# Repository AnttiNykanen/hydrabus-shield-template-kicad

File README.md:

# HydraBus shield template for KiCad

By Antti Nykänen <aon@umetronics.com>

This is a template project for making a [HydraBus](http://hydrabus.com/) shield with [KiCad](http://kicad-pcb.org/). It is based on the [Eagle template](https://github.com/bvernoux/hydrabus/tree/master/hardware/HydraBus_1_0_Shield_Template_Rev0) by Benjamin Vernoux. 

This work is licensed under a [Creative Commons Attribution-ShareAlike 4.0 International License](http://creativecommons.org/licenses/by-sa/4.0/)

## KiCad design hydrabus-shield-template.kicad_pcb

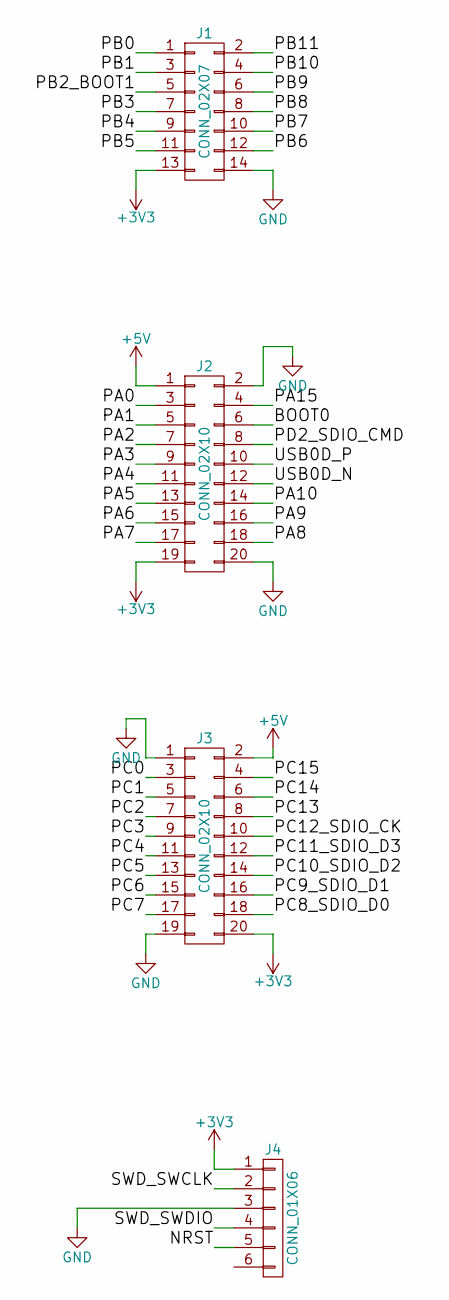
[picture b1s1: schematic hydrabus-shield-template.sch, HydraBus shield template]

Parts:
J1: CONN_02X07; Pin_Header_Straight_2x07
J2, J3: CONN_02X10; Pin_Header_Straight_2x10
J4: CONN_01X06; Pin_Header_Straight_1x06

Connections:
+3V3: J1.13, J2.19, J3.20, J4.1
+5V: J2.1, J3.2
/BOOT0: J2.6
/NRST: J4.5
/PA0: J2.3
/PA1: J2.5
/PA2: J2.7
/PA3: J2.9
/PA4: J2.11
/PA5: J2.13
/PA6: J2.15
/PA7: J2.17
/PA8: J2.18
/PA9: J2.16
/PA10: J2.14
/PA15: J2.4
/PB0: J1.1
/PB1: J1.3
/PB2_BOOT1: J1.5
/PB3: J1.7
/PB4: J1.9
/PB5: J1.11
/PB6: J1.12
/PB7: J1.10
/PB8: J1.8
/PB9: J1.6
/PB10: J1.4
/PB11: J1.2
/PC0: J3.3
/PC1: J3.5
/PC2: J3.7
/PC3: J3.9
/PC4: J3.11
/PC5: J3.13
/PC6: J3.15
/PC7: J3.17
/PC8_SDIO_D0: J3.18
/PC9_SDIO_D1: J3.16
/PC10_SDIO_D2: J3.14
/PC11_SDIO_D3: J3.12
/PC12_SDIO_CK: J3.10
/PC13: J3.8
/PC14: J3.6
/PC15: J3.4
/PD2_SDIO_CMD: J2.8
/SWD_SWCLK: J4.2
/SWD_SWDIO: J4.4
/USB0D_N: J2.12
/USB0D_P: J2.10
GND: J1.14, J2.2, J2.20, J3.1, J3.19, J4.3

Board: 2 copper layers, 4 parts (0 on the bottom side), 3 nets, no tracks yet.

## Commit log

2015-12-17 initial revision
2015-12-18 pcb: rotated J1, added silkscreen labels for pins
2015-12-19 pcb/sch: updated footprints

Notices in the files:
README.md:
cc-by-sa
hydrabus-shield-template.kicad_pcb:
CC BY-SA 4.0
